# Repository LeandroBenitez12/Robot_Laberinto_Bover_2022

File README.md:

The Robot "Bover" Laberinto for the "Liga Nacional de Robotica" in Casares,Bs. As., Argentina

Design 3D --> Design the Robots, Photos and Files

Hardware --> Design of PCB , Sch in Kicad 6

Software --> Codes in C++ Arduino

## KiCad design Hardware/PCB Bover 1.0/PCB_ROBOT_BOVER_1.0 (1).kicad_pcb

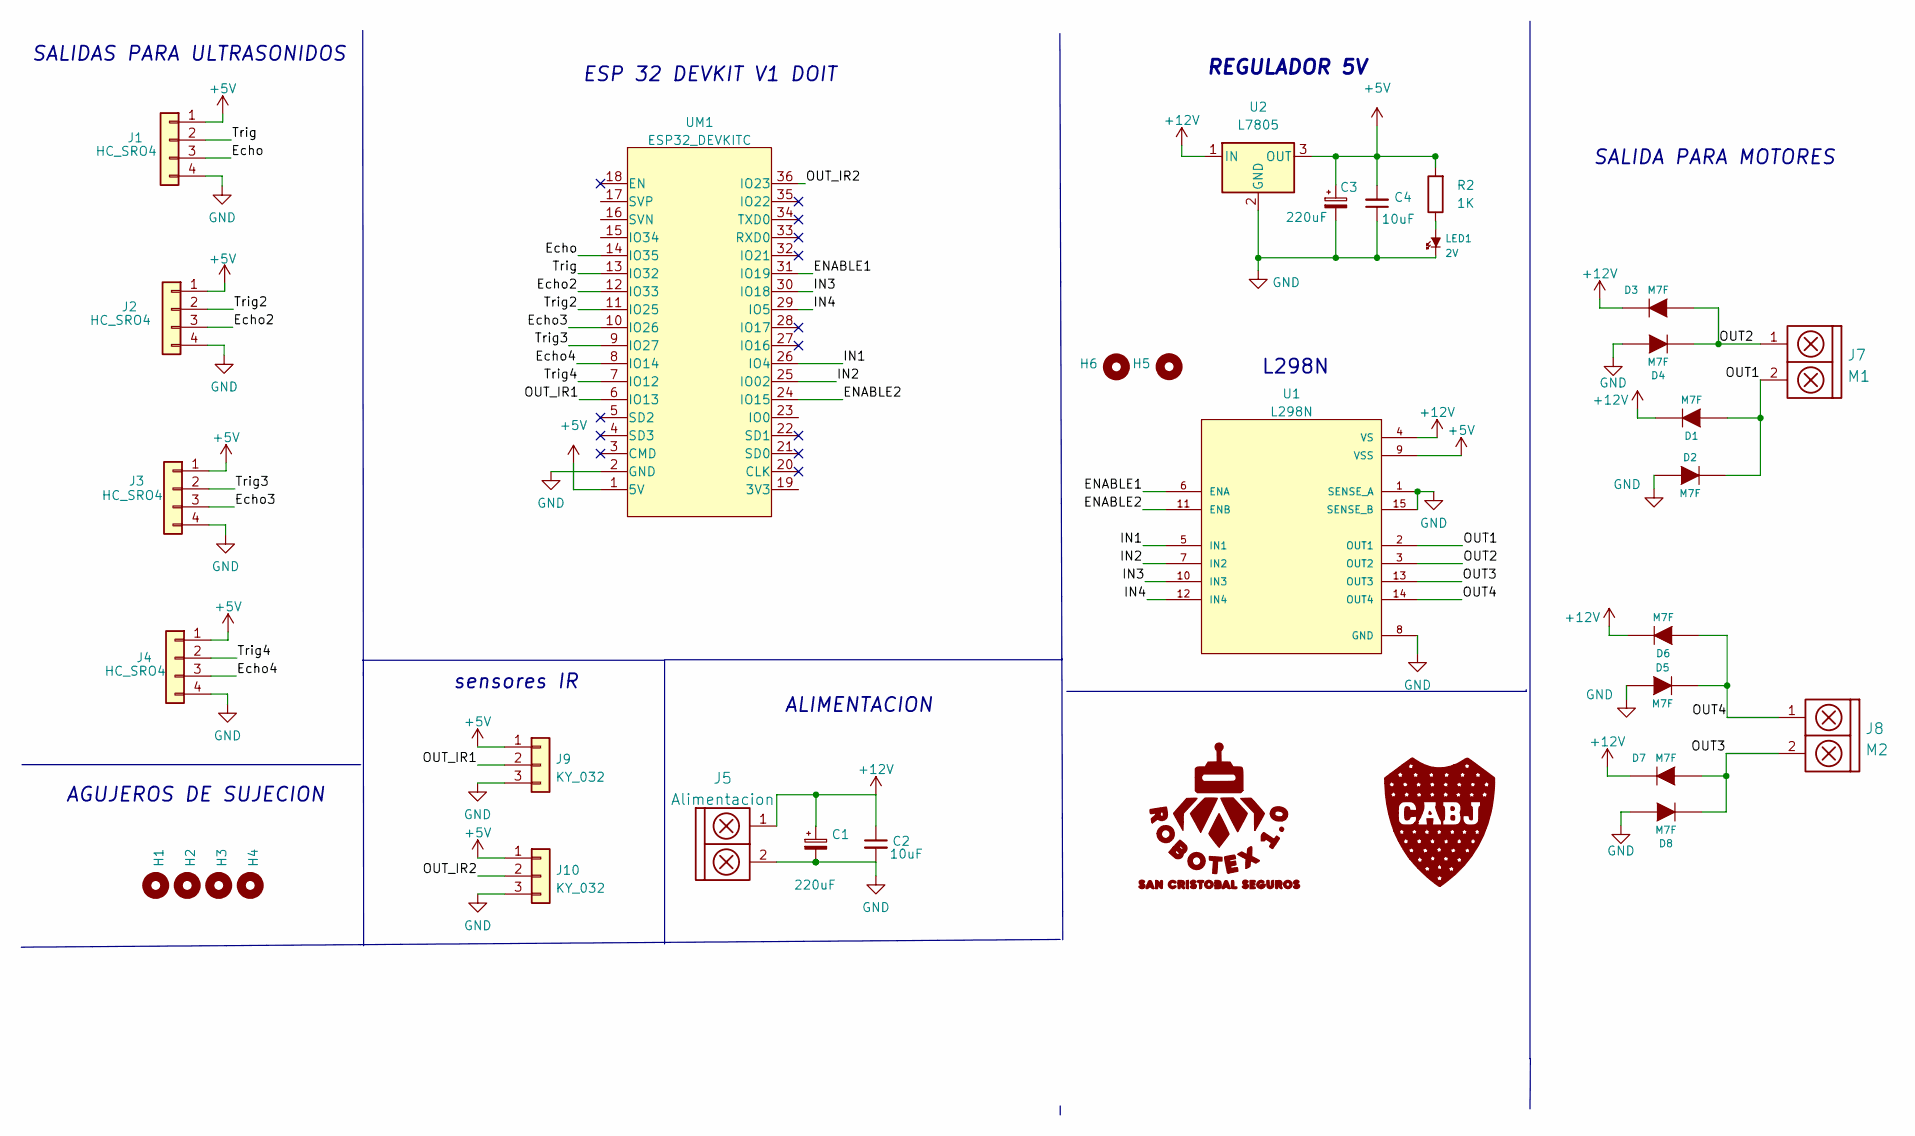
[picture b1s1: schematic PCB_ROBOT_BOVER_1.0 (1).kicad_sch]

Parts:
C1, C3: 220uF; CP_Radial_D8.0mm_P3.80mm
C2, C4: 10uF; C_0805_2012Metric_Pad1.18x1.45mm_HandSolder
D1, D2, D4, D5, D6, D7, D8: M7F; SOD80C
D3: M7F; DO-41
G1: LOGO; logo boca huella.kicad_sym
G2: LOGO RB EXP 1.0; logo rb exp
H1, H2, H3, H4, H5, H6: Mounting_Hole; pad_2mm
J1, J2, J3, J4: HC_SRO4; pin_strip_4
J5: Alimentacion; BORNERA2_AZUL
J7: M1; BORNERA2_AZUL
J8: M2; BORNERA2_AZUL
J9, J10: KY_032; Pin_Strip_3
LED1: 2V; Led_0805
R2: 1K; R_0805
U1: L298N; TO127P2020X500X2100-15
U2: L7805; to220
UM1: ESP32_DEVKITC

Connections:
+5V: C3.1, C4.2, J1.1, J2.1, J3.1, J4.1, J9.1, J10.1, R2.2, U1.9 (VSS), U2.3 (OUT), UM1.1 (5V)
+12V: C1.1, C2.1, D1.2 (K), D3.2 (K), D6.2 (K), D7.2 (K), J5.1, U1.4 (VS), U2.1 (IN)
/ENABLE1: U1.6 (ENA), UM1.31 (IO19)
/ENABLE2: U1.11 (ENB), UM1.24 (IO15)
/Echo: J1.3, UM1.14 (IO35)
/Echo2: J2.3, UM1.12 (IO33)
/Echo3: J3.3, UM1.10 (IO26)
/Echo4: J4.3, UM1.8 (IO14)
/IN1: U1.5 (IN1), UM1.26 (IO4)
/IN2: U1.7 (IN2), UM1.25 (IO02)
/IN3: U1.10 (IN3), UM1.30 (IO18)
/IN4: U1.12 (IN4), UM1.29 (IO5)
/OUT1: D1.1 (A), D2.2 (K), J7.2, U1.2 (OUT1)
/OUT2: D3.1 (A), D4.2 (K), J7.1, U1.3 (OUT2)
/OUT3: D7.1 (A), D8.2 (K), J8.2, U1.13 (OUT3)
/OUT4: D5.2 (K), D6.1 (A), J8.1, U1.14 (OUT4)
/OUT_IR1: J9.2, UM1.6 (IO13)
/OUT_IR2: J10.2, UM1.36 (IO23)
/Trig: J1.2, UM1.13 (IO32)
/Trig2: J2.2, UM1.11 (IO25)
/Trig3: J3.2, UM1.9 (IO27)
/Trig4: J4.2, UM1.7 (IO12)
GND: C1.2, C2.2, D2.1 (A), D4.1 (A), D5.1 (A), D8.1 (A), J1.4, J2.4, J3.4, J4.4, J5.2, J9.3, J10.3, U1.1 (SENSE_A), U1.8 (GND), U1.15 (SENSE_B), UM1.2 (GND)
unnamed: C3.2, C4.1, LED1.2 (K), U2.2 (GND)
unnamed: LED1.1 (A), R2.1

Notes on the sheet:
ALIMENTACION
AGUJEROS DE SUJECION
sensores IR
L298N
ESP 32 DEVKIT V1 DOIT
SALIDAS PARA ULTRASONIDOS
REGULADOR 5V
SALIDA PARA MOTORES

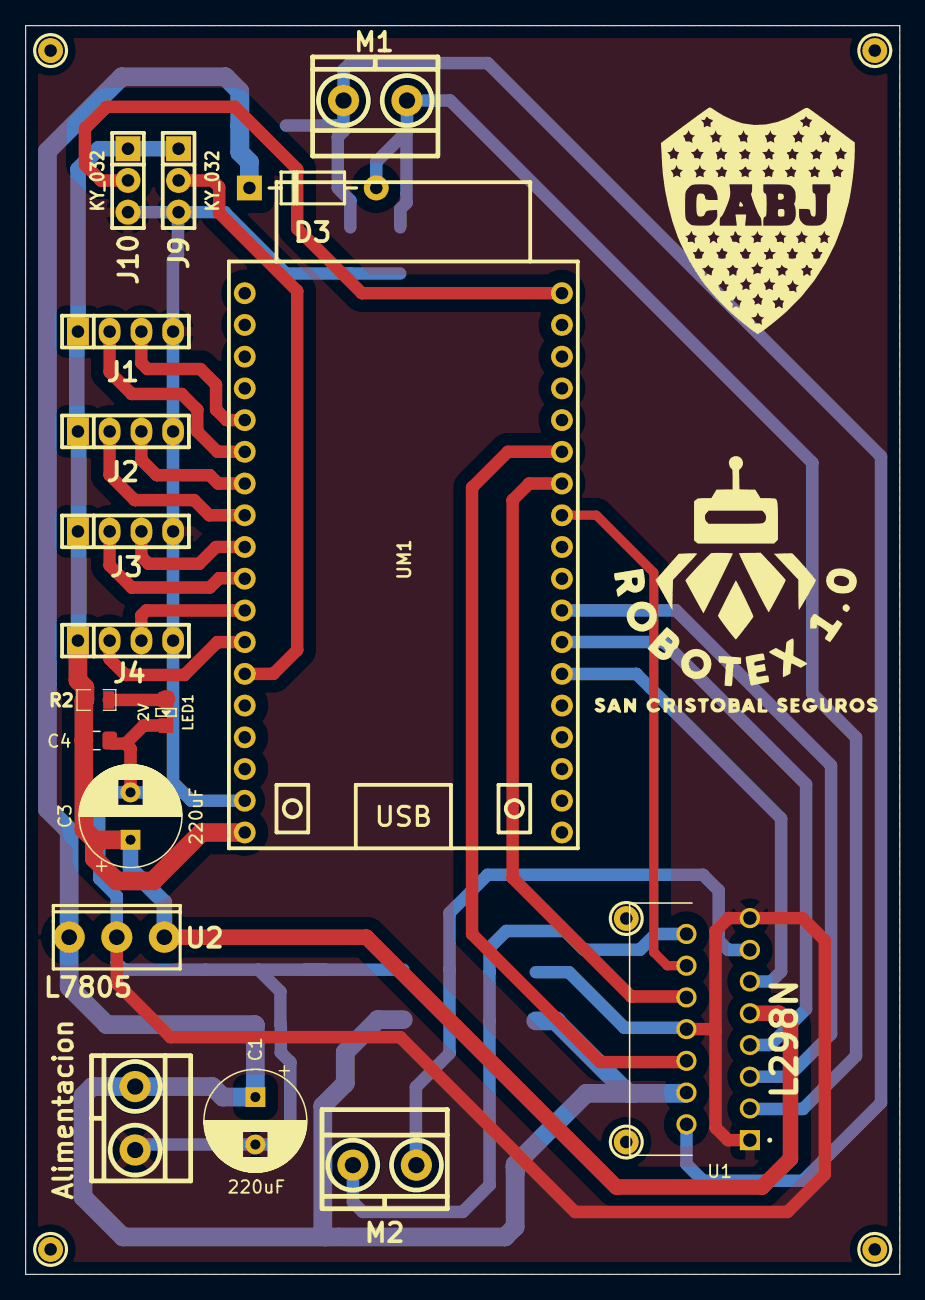
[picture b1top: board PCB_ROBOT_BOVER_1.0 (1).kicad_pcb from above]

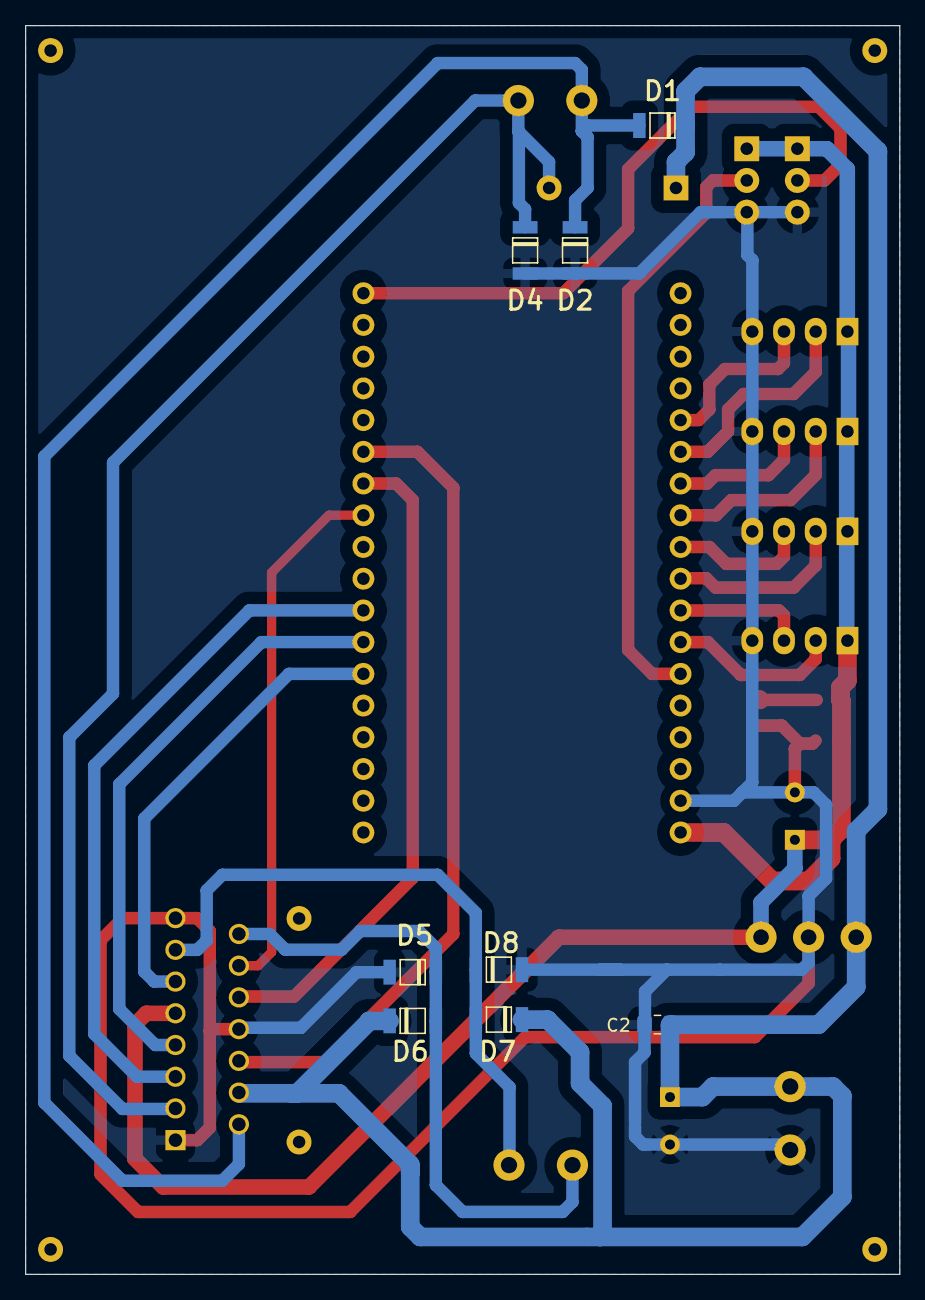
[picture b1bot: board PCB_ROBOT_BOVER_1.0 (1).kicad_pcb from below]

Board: 2 copper layers, 70.0 x 100.0 mm, 34 parts (8 on the bottom side), 25 nets.

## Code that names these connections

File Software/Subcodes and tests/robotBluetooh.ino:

#include "BluetoothSerial.h"


// DEBUG
#define DEBUG 1
// declaramos pines
// motores
#define ENA 15
#define MR1 18
#define MR2 5
#define ENB 19
#define ML1 4
#define ML2 2
// ultrasonidos
#define ECHO1 35
#define ECHO2 33
#define ECHO3 26
#define ECHO4 14
#define TRIG1 32
#define TRIG2 25
#define TRIG3 27
#define TRIG4 12
#define DISTANCIA_MINIMA 15
#define TICK_ULTRASONIDO 20
#define VELOCIDAD 200
int distancia;
int duracion;
// pwm
const int freq = 5000;
const int PWMChannel = 0;
const int resolution = 8;
const int freq2 = 5000;
const int PWMChannel2 = 0;
const int resolution2 = 8;
// Sensores
int SensorDerecha;
int SensorAdelanteIzquierda;
int SensorAdelanteDerecha;
int SensorIzquierda;
int received;// lo que recibe la variable
char receivedChar;// received value will be stored as CHAR in this variable
int periodo = 1000;
unsigned long tiempo_actual = 0;

//---------------------------------------------------------------------------------------------------
//establecemos conexion bluetooth
#if !defined(CONFIG_BT_ENABLED) || !defined(CONFIG_BLUEDROID_ENABLED)
#error Bluetooth is not enabled! Please run `make menuconfig` to and enable it
#endif

BluetoothSerial SerialBT;
//---------------------------------------------------------------------------------------------------
enum CAMINOS
{
  cruce_pasillo,
  cruce_pared,
};
// PIN_SENSORES en una matriz
int pin_sensores_ultrasonido[4][2] = {
    {ECHO1, TRIG1},
    {ECHO2, TRIG2},
    {ECHO3, TRIG3},
    {ECHO4, TRIG4},
};

void AsignacionpinesMOTORES()
{
  pinMode(MR1, OUTPUT);
  pinMode(MR2, OUTPUT);
  pinMode(ML1, OUTPUT);
  pinMode(ML2, OUTPUT);
}
// Asignacion de pines utilizando la matriz para no declarar cada sensor y hacer 100 lines de cod
void asignacionPinesSensores()
{
  for (int fila = 0; fila < 4; fila++)
  {
    int pin_echo = pin_sensores_ultrasonido[fila][0];
    int pin_trig = pin_sensores_ultrasonido[fila][1];
    pinMode(pin_echo, INPUT);
    pinMode(pin_trig, OUTPUT);
    digitalWrite(pin_trig, LOW);
  }
}
void AsignacionpinesPWM()
{
  ledcSetup(PWMChannel, freq, resolution);
  ledcSetup(PWMChannel2, freq2, resolution2);
  ledcAttachPin(ENA, PWMChannel);
  ledcAttachPin(ENB, PWMChannel2);
}

//---------------------------------------------------------------------------------------------------

enum MOTOR_ESTADO
{
  AVANZAR,
  RETROCEDER,
  STOP
};
void Motor(int estado, int pin1, int pin2, int pwm)
{

  ledcWrite(pwm, VELOCIDAD);

  switch (estado)
  {
  case AVANZAR:
    digitalWrite(pin1, LOW);
    digitalWrite(pin2, HIGH);
    break;
  case RETROCEDER:
    digitalWrite(pin1, HIGH );
    digitalWrite(pin2, LOW );
    break;
  case STOP:
    digitalWrite(pin1, LOW);
    digitalWrite(pin2, LOW);
    break;
  }
}

void MotorDer(int estado)
{
  Motor(estado, MR1, MR2, PWMChannel);
}
void MotorIzq(int estado)
{
  Motor(estado, ML1, ML2, PWMChannel2);
}
// HACIA ADELANTE
void Forward()
{
  MotorDer(AVANZAR);
  MotorIzq(AVANZAR);
}
// HACIA ATRAS
void Backward()
{
  MotorDer(RETROCEDER);
  MotorIzq(RETROCEDER);
}
// GIRO SOBRE SU PROPIO EJE A LA DERECHA
void Right()
{
  MotorDer(RETROCEDER);
  MotorIzq(AVANZAR);
}
// GIRO SOBRE SU PROPIO EJE A LA IZQUIERDA
void Left()
{
  MotorDer(AVANZAR);
  MotorIzq(RETROCEDER);
}
// PARAR
void Stop()
{
  MotorDer(STOP);
  MotorIzq(STOP);
}
//-------------------------------------------------------------
int LeerUltrasonidos(int pin_trig, int pin_echo)
{
  long distancia;
  long duracion;
  // SENSOR
  digitalWrite(pin_trig, HIGH);
  delayMicroseconds(10); // Enviamos un pulso de 10us
  digitalWrite(pin_trig, LOW);
  duracion = pulseIn(pin_echo, HIGH);
  distancia = duracion / 58.2;
  return distancia;
}

enum MOVIMIENTOS
{
  ADELANTE,
  ATRAS,
  DERECHA,
  IZQUIERDA,
  PARAR
};
int movimiento = ADELANTE;
int movimiento_anterior = PARAR;
void MovimientodelRobot(int movimiento)
{
  switch (movimiento)
  {
  case ADELANTE:
  {
    Forward();
    break;
  }
  case ATRAS:
  {
    Backward();
    break;
  }
  case IZQUIERDA:
  {
    Left();
    break;
  }
  case DERECHA:
  {
    Right();
    delay(300);
    break;
  }
  case PARAR:
  {
    Stop();
    delay(600);
    break;
  }
  }
}

//-------------------------------------------------------------
void ImprimirEstadoRobot(int movimiento)
{
  String estado_robot = "";

  if (movimiento == ADELANTE)
    estado_robot = "ADELANTE";
  else if (movimiento == ATRAS)
    estado_robot = "ATRAS";
  else if (movimiento == IZQUIERDA)
    estado_robot = "IZQUIERDA";
  else if (movimiento == DERECHA)
    estado_robot = "DERECHA";
  else if (movimiento == PARAR)
    estado_robot = "PARAR";

  Serial.print("movimiento: ");
  Serial.print(estado_robot);
  Serial.print(" | ");
}
void ImprimirDatos(int sd, int sai, int sad, int si)
{
  Serial.print("sd: ");
  Serial.print(sd);
  Serial.print("-  sai: ");
  Serial.print(sai);
  Serial.print(" - sad: ");
  Serial.print(sad);
  Serial.print(" - si: ");
  Serial.println(si);
}
//-------------------------------------------------------------
void setup()
{
  Serial.begin(115200);
  SerialBT.begin("ESP32_Benitez"); //Nombre del Bluetooth
  AsignacionpinesMOTORES();
  asignacionPinesSensores();
  AsignacionpinesPWM();
}
void loop()
{

  if (millis() > tiempo_actual + TICK_ULTRASONIDO)
  {
    tiempo_actual = millis();
   // SensorDerecha = LeerUltrasonidos(TRIG1, ECHO1);
   SensorAdelanteIzquierda = LeerUltrasonidos(TRIG2, ECHO2);
    //SensorAdelanteDerecha = LeerUltrasonidos(TRIG3, ECHO3);
   // SensorIzquierda = LeerUltrasonidos(TRIG4, ECHO4);
  }

  // logica-algoritmo

  receivedChar = (char)SerialBT.read();

  if (Serial.available()) {
    SerialBT.write(Serial.read());
  }
  if (SerialBT.available()) {

    if (SensorAdelanteIzquierda > DISTANCIA_MINIMA) {
      Serial.print ("Received:");//print on serial monitor
      Serial.println(receivedChar);//print on serial monitor

      if (receivedChar == 'F')
      {
        Forward();
      }
      if (receivedChar == 'G')
      {
        Backward();
      }
      if (receivedChar == 'L')
      {
        Left();
      }
      if (receivedChar == 'R')
      {
        Right();
      }
      if (receivedChar == 'S')
      {
        Stop();
      }
    } else {
      movimiento=IZQUIERDA;
    }
  }

  if (movimiento != movimiento_anterior)
  {
    MovimientodelRobot(movimiento);
    movimiento_anterior = movimiento;
  }
  ImprimirEstadoRobot(movimiento);
  ImprimirDatos(SensorDerecha, SensorAdelanteIzquierda, SensorAdelanteDerecha, SensorIzquierda);
}

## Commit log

2022-08-16 Agregando cositas
2022-08-16 Tenia un error los codigos
2022-08-17 Pequeños cambios
2022-08-17 agreue un espacio
2022-08-17 aGREGUE UN COMENTARIO
2022-08-18 Ad the Design 3D
2022-08-24 Rama nueva
2022-09-04 add the designs and PCB edit
2022-09-04 Actuale codigos de Bover para ayacucho
2022-09-04 agregue img y 3d
